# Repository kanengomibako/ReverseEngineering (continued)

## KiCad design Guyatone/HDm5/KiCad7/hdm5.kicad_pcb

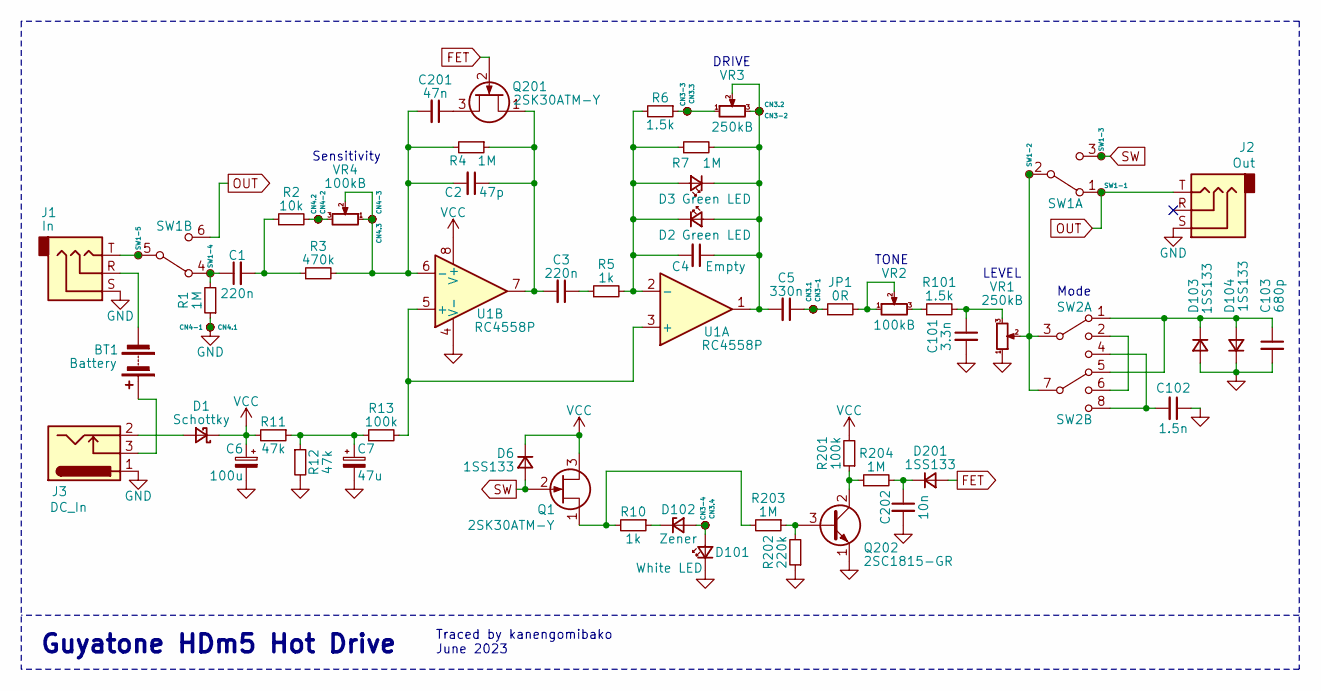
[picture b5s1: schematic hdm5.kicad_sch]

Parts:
BT1: Battery; PinHeader_1x02_P2.54mm_Vertical
C1, C3: 220n; my_C_Rect1_P5.00mm
C2: 47p; my_C_Disc_P2.50mm
C4: Empty; my_C_Disc_P2.50mm
C5: 330n; my_C_Rect1_P5.00mm
C6: 100u; my_C_D5.0mm_P2.50mm
C7: 47u; my_C_D5.0mm_P2.50mm
C101: 3.3n; my_C_Disc_P2.50mm
C102: 1.5n; my_C_Disc_P2.50mm
C103: 680p; C_Rect_L11.0mm_W2.8mm_P10.00mm_MKT
C201: 47n; my_C_Rect1_P5.00mm
C202: 10n; my_C_Rect1_P5.00mm
CN3-1, CN3-2, CN3-3, CN3-4, CN3.1, CN3.2, CN3.3, CN3.4, CN4-1, CN4-2, CN4-3, CN4.1, CN4.2, CN4.3: tp; my_SmallestPad_0-72mmDrill
D1: Schottky; D_A-405_P7.62mm_Horizontal
D2, D3: Green LED; my_LED_3mm
D6, D103, D104, D201: 1SS133; D_A-405_P5.08mm_Vertical_KathodeUp
D101: White LED; my_LED_3mm
D102: Zener; D_A-405_P5.08mm_Vertical_KathodeUp
J1: In; Audio_Jack_EX
J2: Out; Audio_Jack_EX
J3: DC_In; my_DC_Jack
JP1: 0R; R_Axial_DIN0204_L3.6mm_D1.6mm_P5.08mm_Vertical
Q1, Q201: 2SK30ATM-Y; TO-92L_Wide
Q202: 2SC1815-GR; TO-92L_Wide
R1, R203, R204: 1M; R_Axial_DIN0204_L3.6mm_D1.6mm_P5.08mm_Vertical
R2: 10k; R_Axial_DIN0204_L3.6mm_D1.6mm_P5.08mm_Vertical
R3: 470k; R_Axial_DIN0204_L3.6mm_D1.6mm_P2.54mm_Vertical
R4, R7: 1M; R_Axial_DIN0204_L3.6mm_D1.6mm_P2.54mm_Vertical
R5, R10: 1k; R_Axial_DIN0204_L3.6mm_D1.6mm_P5.08mm_Vertical
R6: 1.5k; R_Axial_DIN0204_L3.6mm_D1.6mm_P2.54mm_Vertical
R11, R12: 47k; R_Axial_DIN0204_L3.6mm_D1.6mm_P5.08mm_Vertical
R13: 100k; R_Axial_DIN0204_L3.6mm_D1.6mm_P5.08mm_Vertical
R101: 1.5k; R_Axial_DIN0204_L3.6mm_D1.6mm_P5.08mm_Vertical
R201: 100k; R_Axial_DIN0204_L3.6mm_D1.6mm_P2.54mm_Vertical
R202: 220k; R_Axial_DIN0204_L3.6mm_D1.6mm_P2.54mm_Vertical
SW1: SW1; PinHeader_2x03_P2.54mm_Vertical
SW1-1, SW1-2, SW1-3, SW1-4, SW1-5: tp; my_SmallestPad_0-72mmDrill
SW2: SW2; PinHeader_2x04_P2.54mm_Vertical
U1: RC4558P; DIP-8_W7.62mm_Socket
VR1, VR3: 250kB; PinHeader_1x03_P2.54mm_Vertical
VR2, VR4: 100kB; PinHeader_1x03_P2.54mm_Vertical

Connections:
FET: D201.2 (A), Q201.2 (G)
GND: C6.2, C7.2, C101.2, C102.1, C103.2, C202.2, CN4-1.1, CN4.1.1, D101.1 (K), D103.2 (A), D104.1 (K), J1.S, J2.S, J3.1, Q202.1 (E), R1.1, R12.2, R202.1, U1.4 (V-), VR1.1
unnamed: BT1.1 (+), J3.3
unnamed: BT1.2 (-), J1.R
unnamed: C1.1, R1.2, SW1.4 (A), SW1-4.1
unnamed: C1.2, R2.1, R3.1
unnamed: C3.1, R5.1
unnamed: C5.1, CN3-1.1, CN3.1.1, JP1.1
unnamed: C7.1, R11.1, R12.1, R13.1
unnamed: C101.1, R101.2, VR1.3
unnamed: C102.2, SW2.4, SW2.8
unnamed: CN3-3.1, CN3.3.1, R6.1, VR3.1
unnamed: CN4-2.1, CN4.2.1, R2.2, VR4.3
unnamed: D1.2 (A), J3.2
unnamed: C4.1, C5.2, CN3-2.1, CN3.2.1, D2.2 (A), D3.1 (K), R7.2, U1.1, VR3.2, VR3.3
unnamed: C4.2, D2.1 (K), D3.2 (A), R5.2, R6.2, R7.1, U1.2 (-)
unnamed: CN3-4.1, CN3.4.1, D101.2 (A), D102.2 (A)
unnamed: D102.1 (K), R10.1
unnamed: C103.1, D103.1 (K), D104.2 (A), SW2.1, SW2.5
unnamed: C202.1, D201.1 (K), R204.2
unnamed: J1.T, SW1.5 (B), SW1-5.1
unnamed: JP1.2, VR2.1, VR2.2
unnamed: Q1.1 (S), R10.2, R203.2
unnamed: C201.1, Q201.3 (D)
unnamed: C2.1, C3.2, Q201.1 (S), R4.1, U1.7
unnamed: Q202.3 (B), R202.2, R203.1
unnamed: Q202.2 (C), R201.1, R204.1
unnamed: R101.1, VR2.3
unnamed: SW1.2 (B), SW1-2.1, SW2.3, SW2.7, VR1.2
unnamed: SW2.2, SW2.6
unnamed: R13.2, U1.3 (+), U1.5 (+)
unnamed: C2.2, C201.2, CN4-3.1, CN4.3.1, R3.2, R4.2, U1.6 (-), VR4.1, VR4.2
OUT: J2.T, SW1.1 (A), SW1.6 (C), SW1-1.1
SW: D6.2 (A), Q1.2 (G), SW1.3 (C), SW1-3.1
VCC: C6.1, D1.1 (K), D6.1 (K), Q1.3 (D), R11.2, R201.2, U1.8 (V+)

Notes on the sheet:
TONE
Guyatone HDm5 Hot Drive
Mode
Sensitivity
DRIVE
Traced by kanengomibako June 2023
LEVEL

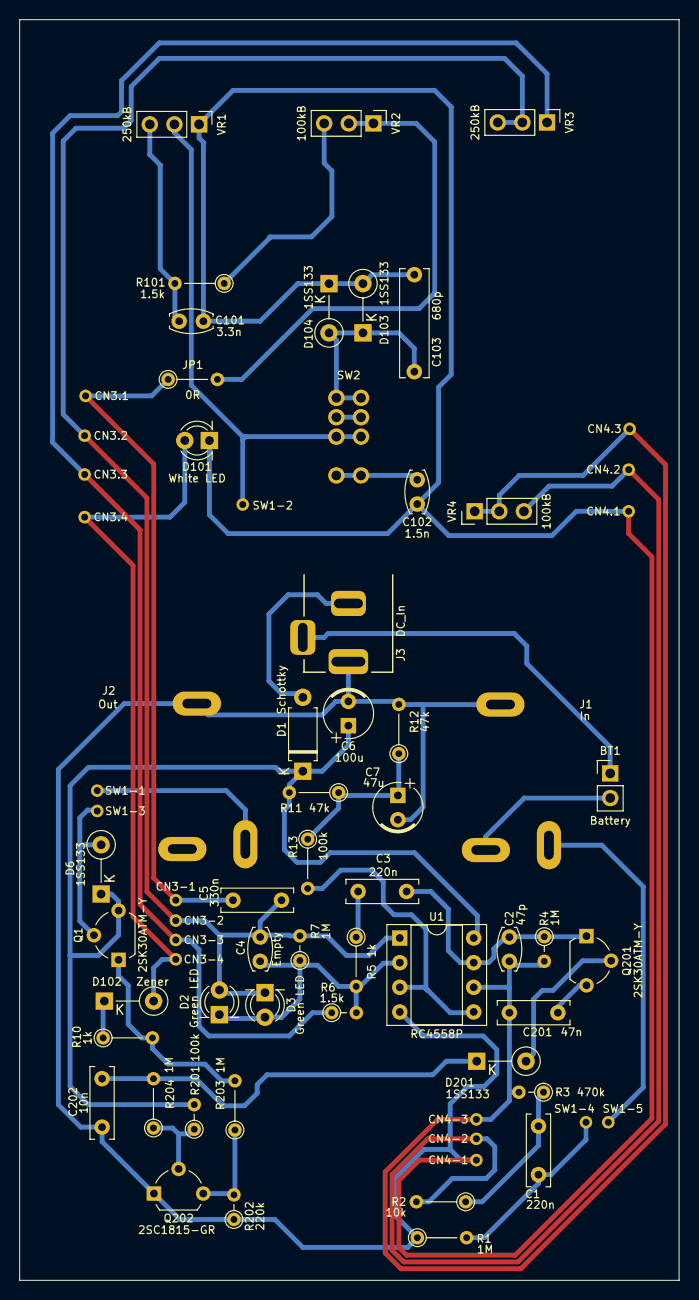
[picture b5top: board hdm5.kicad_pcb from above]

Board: 2 copper layers, 68.0 x 130.0 mm, 70 parts (0 on the bottom side), 35 nets.

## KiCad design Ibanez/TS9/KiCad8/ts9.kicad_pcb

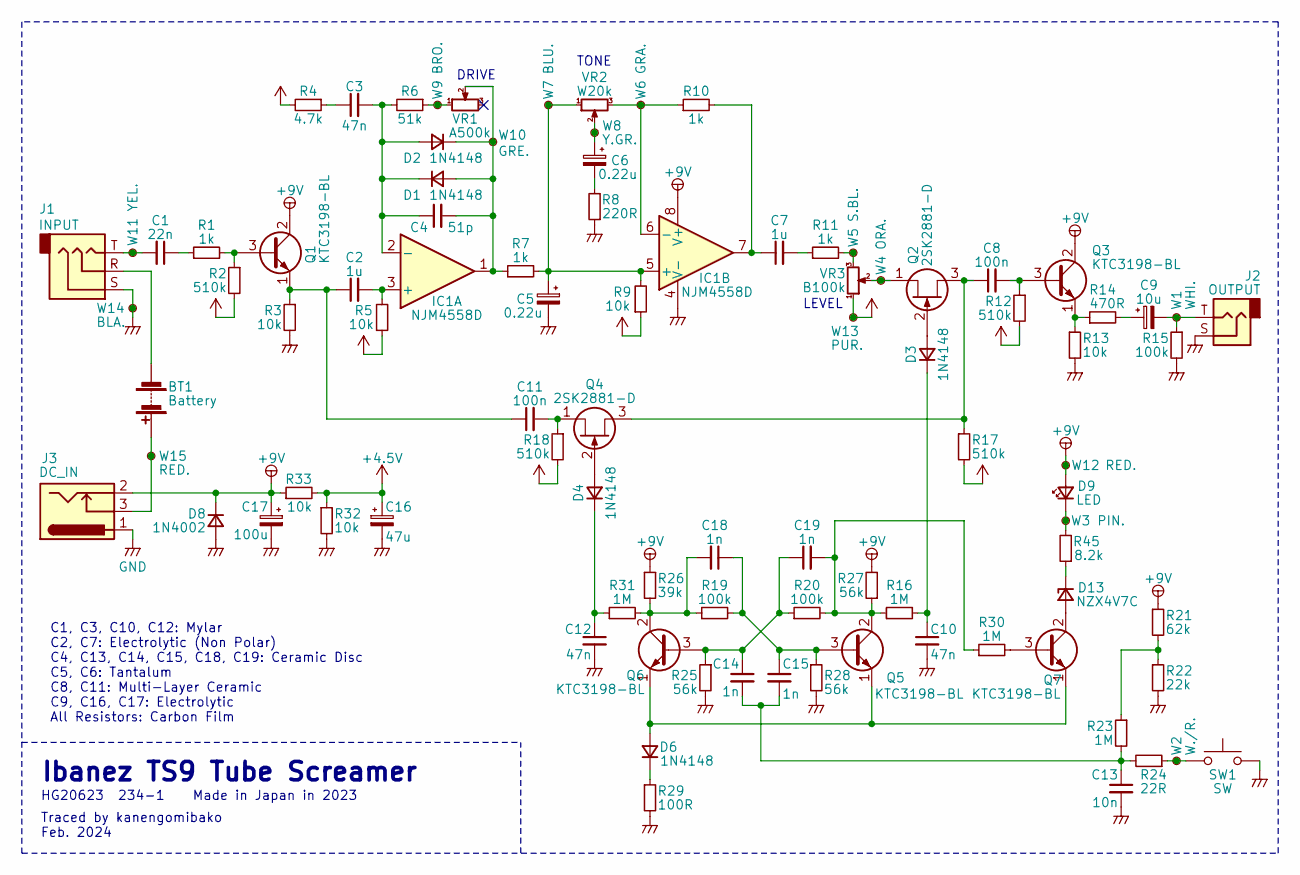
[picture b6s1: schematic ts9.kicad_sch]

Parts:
BT1: Battery; my_conn
C1: 22n; C_Disc_D4.3mm_W1.9mm_P5.00mm
C2, C7: 1u; my_C_NP_P2.50mm
C3, C10, C12: 47n; C_Disc_D4.3mm_W1.9mm_P5.00mm
C4: 51p; C_Disc_D3.0mm_W1.6mm_P2.50mm
C5: 0.22u; CP_Radial_Tantal_D4.5mm_P5.00mm
C6: 0.22u; CP_Radial_Tantal_D4.5mm_P2.50mm
C8, C11: 100n; C_Axial_L3.8mm_D2.6mm_P7.50mm_Horizontal
C9: 10u; my_C_D5.0mm_P2.50mm
C13: 10n; C_Disc_D4.3mm_W1.9mm_P5.00mm
C14, C15, C18, C19: 1n; C_Disc_D4.3mm_W1.9mm_P5.00mm
C16: 47u; my_C_D5.0mm_P2.50mm
C17: 100u; CP_Radial_D8.0mm_P5.00mm
D1, D2: 1N4148; D_DO-35_SOD27_P3.81mm_Vertical_AnodeUp
D3, D4, D6: 1N4148; D_T-1_P5.08mm_Horizontal
D8: 1N4002; D_DO-35_SOD27_P10.16mm_Horizontal
D9: LED; my_conn
D13: NZX4V7C; D_T-1_P5.08mm_Horizontal
IC1: NJM4558D; DIP-8_W7.62mm
J1: INPUT
J2: OUTPUT
J3: DC_IN; my_DC_Jack
Q1, Q3, Q5, Q6, Q7: KTC3198-BL; TO-92_Inline_Wide
Q2, Q4: 2SK2881-D; TO-92_Inline_Wide
R1, R7, R10, R11: 1k; R_Axial_DIN0204_L3.6mm_D1.6mm_P5.08mm_Horizontal
R2, R12, R17, R18: 510k; R_Axial_DIN0204_L3.6mm_D1.6mm_P5.08mm_Horizontal
R3, R13, R32, R33: 10k; R_Axial_DIN0204_L3.6mm_D1.6mm_P5.08mm_Horizontal
R4: 4.7k; my_R_P6mm_Horizontal
R5: 10k; my_R_P6mm_Horizontal
R6: 51k; R_Axial_DIN0204_L3.6mm_D1.6mm_P5.08mm_Horizontal
R8: 220R; R_Axial_DIN0204_L3.6mm_D1.6mm_P5.08mm_Horizontal
R9: 10k; R_Axial_DIN0204_L3.6mm_D1.6mm_P7.62mm_Horizontal
R14: 470R; R_Axial_DIN0204_L3.6mm_D1.6mm_P5.08mm_Horizontal
R15, R19, R20: 100k; R_Axial_DIN0204_L3.6mm_D1.6mm_P5.08mm_Horizontal
R16, R23, R30, R31: 1M; R_Axial_DIN0204_L3.6mm_D1.6mm_P5.08mm_Horizontal
R21: 62k; R_Axial_DIN0204_L3.6mm_D1.6mm_P5.08mm_Horizontal
R22: 22k; R_Axial_DIN0204_L3.6mm_D1.6mm_P5.08mm_Horizontal
R24: 22R; R_Axial_DIN0204_L3.6mm_D1.6mm_P5.08mm_Horizontal
R25, R27, R28: 56k; R_Axial_DIN0204_L3.6mm_D1.6mm_P5.08mm_Horizontal
R26: 39k; R_Axial_DIN0204_L3.6mm_D1.6mm_P5.08mm_Horizontal
R29: 100R; R_Axial_DIN0204_L3.6mm_D1.6mm_P5.08mm_Horizontal
R45: 8.2k; R_Axial_DIN0204_L3.6mm_D1.6mm_P5.08mm_Horizontal
SW1: SW
VR1: A500k
VR2: W20k
VR3: B100k
W1: WHI.; my_WirePad_0-8mmDrill
W2: W./R.; my_WirePad_0-8mmDrill
W3: PIN.; my_WirePad_0-8mmDrill
W4: ORA.; my_WirePad_0-8mmDrill
W5: S.BL.; my_WirePad_0-8mmDrill
W6: GRA.; my_WirePad_0-8mmDrill
W7: BLU.; my_WirePad_0-8mmDrill
W8: Y.GR.; my_WirePad_0-8mmDrill
W9: BRO.; my_WirePad_0-8mmDrill
W10: GRE.; my_WirePad_0-8mmDrill
W11: YEL.; my_WirePad_0-8mmDrill
W12, W15: RED.; my_WirePad_0-8mmDrill
W13: PUR.; my_WirePad_0-8mmDrill
W14: BLA.; my_WirePad_0-8mmDrill

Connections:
+4.5V: C16.1, R2.2, R4.2, R5.1, R9.1, R12.2, R17.2, R18.2, R32.1, R33.2, VR3.1, W13.1
+9V: C17.1, D8.1 (K), D9.2 (A), IC1.8 (V+), J3.2, Q1.2 (C), Q3.2 (C), R21.1, R26.1, R27.2, R33.1, W12.1
GND: C5.2, C10.2, C12.2, C13.2, C16.2, C17.2, D8.2 (A), IC1.4 (V-), J1.S, J2.S, J3.1, R3.2, R8.1, R13.2, R15.2, R22.2, R25.2, R28.2, R29.2, R32.2, SW1.2, W14.1
unnamed: BT1.2 (-), J1.R
unnamed: C1.1, R1.1
unnamed: C1.2, J1.T, W11.1
unnamed: C3.1, R4.1
unnamed: C6.1, VR2.2, W8.1
unnamed: C6.2, R8.2
unnamed: C7.1, IC1.7, R10.2
unnamed: C7.2, R11.1
unnamed: C9.1, R14.2
unnamed: C9.2, J2.T, R15.1, W1.1
unnamed: C13.1, C14.2, C15.2, R23.2, R24.2
unnamed: C4.2, D1.2 (A), D2.1 (K), IC1.1, R7.1, VR1.2, W10.1
unnamed: C3.2, C4.1, D1.1 (K), D2.2 (A), IC1.2 (-), R6.2
unnamed: D3.2 (A), Q2.2 (G)
unnamed: C10.1, D3.1 (K), R16.2
unnamed: D4.2 (A), Q4.2 (G)
unnamed: C12.1, D4.1 (K), R31.1
unnamed: D6.2 (A), Q5.1 (E), Q6.1 (E), Q7.1 (E)
unnamed: D6.1 (K), R29.1
unnamed: D13.2 (A), Q7.2 (C)
unnamed: D13.1 (K), R45.1
unnamed: C2.2, IC1.3 (+), R5.2
unnamed: C5.1, IC1.5 (+), R7.2, R9.2, VR2.1, W7.1
unnamed: IC1.6 (-), R10.1, VR2.3, W6.1
unnamed: BT1.1 (+), J3.3, W15.1
unnamed: Q1.3 (B), R1.2, R2.1
unnamed: C2.1, C11.1, Q1.1 (E), R3.1
unnamed: C8.1, Q2.3 (D), Q4.3 (D), R17.1
unnamed: Q2.1 (S), VR3.2, W4.1
unnamed: C8.2, Q3.3 (B), R12.1
unnamed: Q3.1 (E), R13.1, R14.1
unnamed: C11.2, Q4.1 (S), R18.1
unnamed: C15.1, C18.1, Q5.3 (B), R19.2, R28.1
unnamed: C19.2, Q5.2 (C), R16.1, R20.2, R27.1, R30.1
unnamed: C14.1, C19.1, Q6.3 (B), R20.1, R25.1
unnamed: C18.2, Q6.2 (C), R19.1, R26.2, R31.2
unnamed: Q7.3 (B), R30.2
unnamed: R6.1, VR1.1, W9.1
unnamed: R11.2, VR3.3, W5.1
unnamed: R21.2, R22.1, R23.1
unnamed: R24.1, SW1.1, W2.1
unnamed: D9.1 (K), R45.2, W3.1

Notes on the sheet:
Ibanez TS9 Tube Screamer
HG20623 234-1 Made in Japan in 2023
DRIVE
Traced by kanengomibako Feb. 2024
LEVEL
TONE
C1, C3, C10, C12: Mylar C2, C7: Electrolytic (Non Polar) C4, C13, C14, C15, C18, C19: Ceramic Disc C5, C6: Tantalum C8, C11: Multi-Layer Ceramic C9, C16, C17: Electrolytic All Resistors: Carbon Film

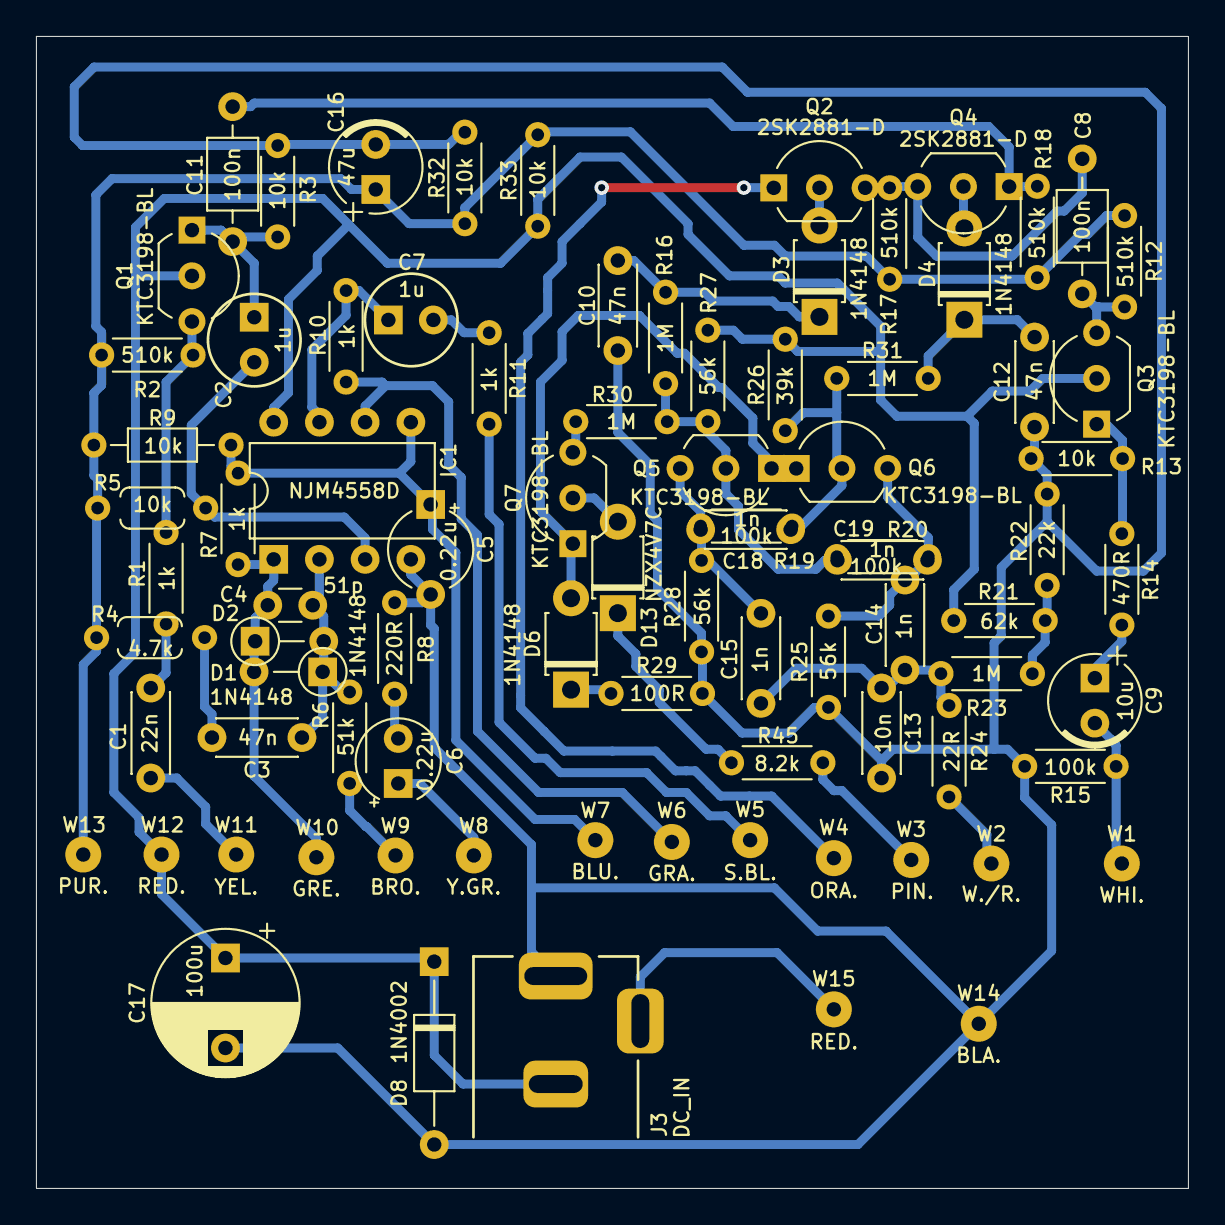
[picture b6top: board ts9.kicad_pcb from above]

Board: 2 copper layers, 64.0 x 64.0 mm, 84 parts (0 on the bottom side), 44 nets.

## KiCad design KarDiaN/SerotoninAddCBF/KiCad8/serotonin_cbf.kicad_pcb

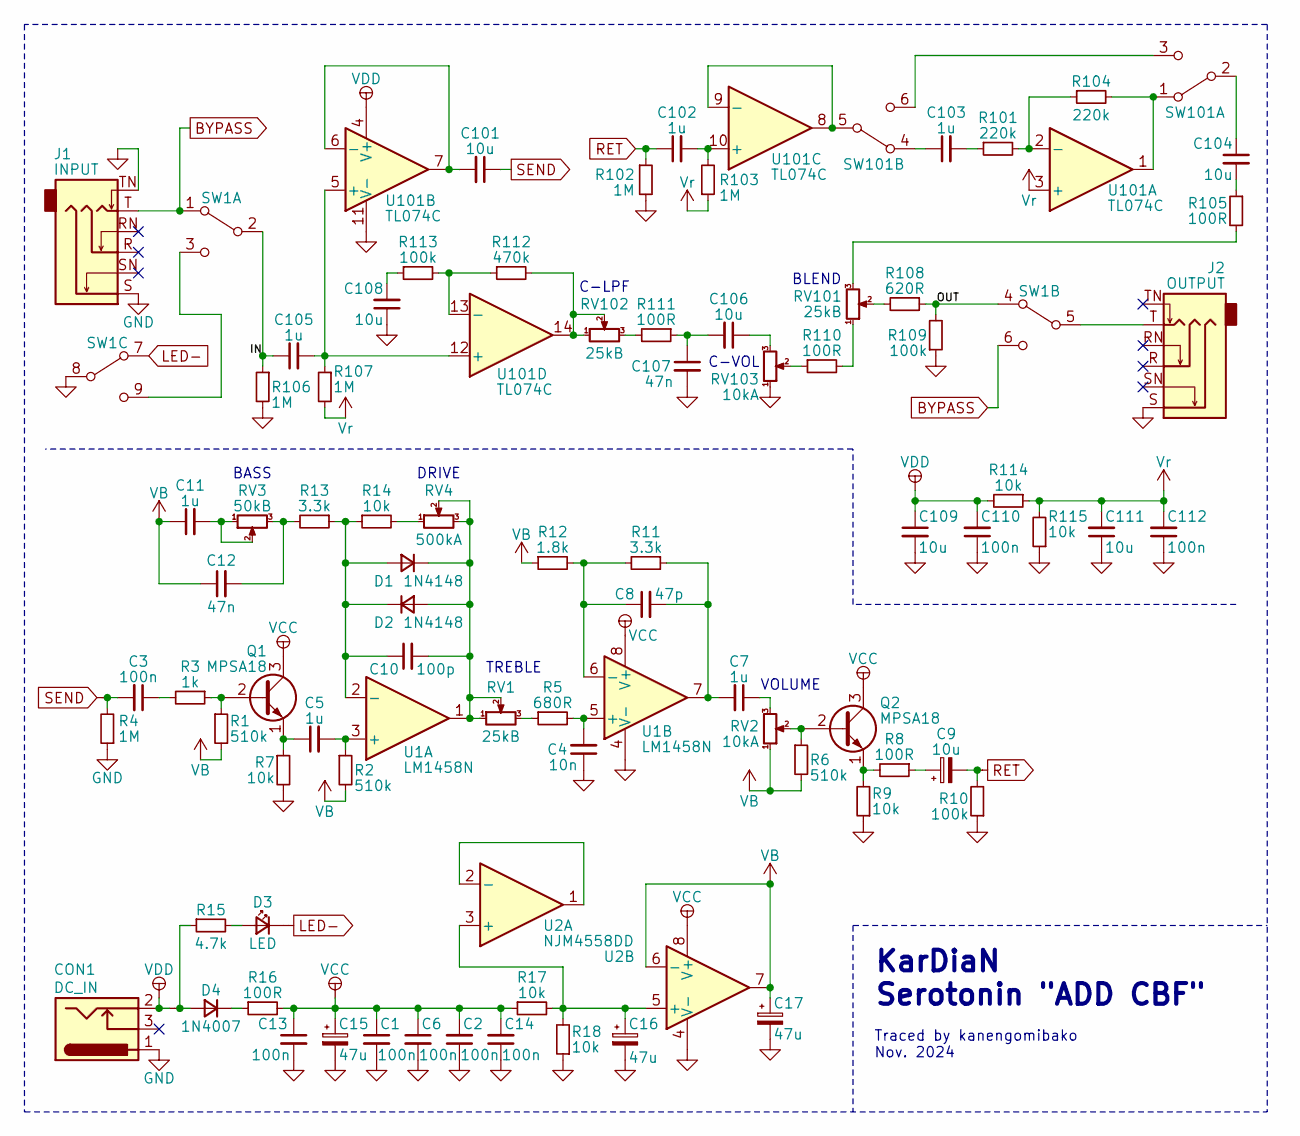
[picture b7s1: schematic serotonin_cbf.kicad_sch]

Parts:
C1, C2, C6, C13, C14: 100n; C_Rect_L7.0mm_W2.0mm_P5.00mm
C3: 100n; R_Axial_DIN0414_L11.9mm_D4.5mm_P15.24mm_Horizontal
C4: 10n; C_Rect_L7.0mm_W2.0mm_P5.00mm
C5, C11: 1u; C_Rect_L7.0mm_W2.0mm_P5.00mm
C7: 1u; R_Axial_DIN0414_L11.9mm_D4.5mm_P15.24mm_Horizontal
C8: 47p; C_Rect_L7.0mm_W2.0mm_P5.00mm
C9: 10u; CP_Radial_D8.0mm_P2.50mm
C10: 100p; C_Rect_L7.0mm_W2.0mm_P5.00mm
C12: 47n; C_Rect_L7.0mm_W2.0mm_P5.00mm
C15, C16, C17: 47u; CP_Radial_D8.0mm_P2.50mm
C101, C104, C106, C108, C109, C111: 10u; C_1206_3216Metric
C102, C103, C105: 1u; C_0805_2012Metric
C107: 47n; C_0805_2012Metric
C110, C112: 100n; C_0805_2012Metric
CN1: 006; my_conn
CN2: LED; my_conn
CN3: IN; my_conn
CN4: OUT; my_conn
CON1: DC_IN; my_DC_Jack
D1, D2: 1N4148; my_D_P5.08mm_Horizontal
D3: LED; my_LED_5mm
D4: 1N4007; D_DO-35_SOD27_P7.62mm_Horizontal
J1: INPUT; my_Phone_Jack_Daier
J2: OUTPUT; my_Phone_Jack_Daier
Q1, Q2: MPSA18; TO-92_Inline_Wide
R1, R2, R6: 510k; R_Axial_DIN0207_L6.3mm_D2.5mm_P10.16mm_Horizontal
R3: 1k; R_Axial_DIN0414_L11.9mm_D4.5mm_P15.24mm_Horizontal
R4: 1M; R_Axial_DIN0207_L6.3mm_D2.5mm_P10.16mm_Horizontal
R5: 680R; R_Axial_DIN0414_L11.9mm_D4.5mm_P15.24mm_Horizontal
R7, R9, R14, R17, R18: 10k; R_Axial_DIN0207_L6.3mm_D2.5mm_P10.16mm_Horizontal
R8, R16: 100R; R_Axial_DIN0207_L6.3mm_D2.5mm_P10.16mm_Horizontal
R10: 100k; R_Axial_DIN0207_L6.3mm_D2.5mm_P10.16mm_Horizontal
R11, R13: 3.3k; R_Axial_DIN0207_L6.3mm_D2.5mm_P10.16mm_Horizontal
R12: 1.8k; R_Axial_DIN0207_L6.3mm_D2.5mm_P10.16mm_Horizontal
R15: 4.7k; R_Axial_DIN0207_L6.3mm_D2.5mm_P10.16mm_Horizontal
R101, R104: 220k; R_0805_2012Metric
R102, R103, R106, R107: 1M; R_0805_2012Metric
R105, R110, R111: 100R; R_0805_2012Metric
R108: 620R; R_0805_2012Metric
R109, R113: 100k; R_0805_2012Metric
R112: 470k; R_0805_2012Metric
R114, R115: 10k; R_0805_2012Metric
RV1: 25kB; my_pot_5mm
RV2: 10kA; my_pot_5mm
RV3: 50kB; my_pot_5mm
RV4: 500kA; my_pot_5mm
RV101, RV102: 25kB; PinHeader_1x03_P2.54mm_Vertical
RV103: 10kA; PinHeader_1x03_P2.54mm_Vertical
SW1: SW1; my_sw_3pdt
SW101: SW101; PinHeader_2x03_P2.54mm_Vertical
U1: LM1458N; DIP-8_W7.62mm
U2: NJM4558DD; DIP-8_W7.62mm
U101: TL074C; SO-14_5.3x10.2mm_P1.27mm

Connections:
/IN: C105.1, R106.1, SW1.2 (B)
/OUT: R108.1, R109.2, SW1.4 (A)
BYPASS: J1.T, SW1.1 (A), SW1.6 (C)
GND: C1.2, C2.1, C4.1, C6.2, C13.2, C14.1, C15.2, C16.2, C17.2, C107.2, C108.1, C109.2, C110.1, C111.1, C112.1, CON1.1, J1.S, J1.TN, J2.S, R4.1, R7.2, R9.1, R10.1, R18.1, R102.2, R106.2, R109.1, R115.1, RV103.1, SW1.8 (B), U1.4 (V-), U2.4 (V-), U101.11 (V-); also elsewhere on the board
LED-: CN2.1, SW1.7 (A)
unnamed: C3.1, R3.2
unnamed: C3.2, CN3.2, R4.2
unnamed: C7.1, RV2.3
unnamed: C7.2, C8.2, R11.1, U1.7
unnamed: C9.1, R8.1
unnamed: C9.2, CN4.2, R10.2
unnamed: C11.2, RV3.1, RV3.2
unnamed: C12.2, R13.2, RV3.3
unnamed: C103.2, R101.1
unnamed: C104.2, R105.1
unnamed: C106.1, RV103.3
unnamed: C106.2, C107.1, R111.1
unnamed: C108.2, R113.1
unnamed: C10.1, D1.2 (A), D2.1 (K), R13.1, R14.1, U1.2 (-)
unnamed: C10.2, D1.1 (K), D2.2 (A), RV1.1, RV1.2, RV4.2, RV4.3, U1.1
unnamed: D3.2 (A), R15.2
unnamed: CN2.2, D3.1 (K)
unnamed: CN1.2, D4.2 (A), R15.1
unnamed: D4.1 (K), R16.1
unnamed: Q1.2 (B), R1.1, R3.1
unnamed: C5.1, Q1.1 (E), R7.1
unnamed: Q2.2 (B), R6.1, RV2.2
unnamed: Q2.1 (E), R8.2, R9.2
unnamed: R5.1, RV1.3
unnamed: R14.2, RV4.1
unnamed: R105.2, RV101.3
unnamed: R108.2, RV101.2
unnamed: R110.1, RV103.2
unnamed: R110.2, RV101.1
unnamed: R111.2, RV102.3
unnamed: R112.2, RV102.1, RV102.2, U101.14
unnamed: SW1.3 (C), SW1.9 (C)
unnamed: J2.T, SW1.5 (B)
unnamed: R104.2, SW101.1 (A), U101.1
unnamed: C104.1, SW101.2 (B)
unnamed: SW101.3 (C), SW101.6 (C)
unnamed: C103.1, SW101.4 (A)
unnamed: SW101.5 (B), U101.8, U101.9 (-)
unnamed: C5.2, R2.1, U1.3 (+)
unnamed: C4.2, R5.2, U1.5 (+)
unnamed: C8.1, R11.2, R12.2, U1.6 (-)
unnamed: C16.1, R17.2, R18.2, U2.3 (+), U2.5 (+)
unnamed: U2.1, U2.2 (-)
unnamed: R101.2, R104.1, U101.2 (-)
unnamed: C105.2, R107.1, U101.5 (+), U101.12 (+)
unnamed: C101.2, U101.6 (-), U101.7
unnamed: C102.2, R103.2, U101.10 (+)
unnamed: R112.1, R113.2, U101.13 (-)
RET: C102.1, CN4.1, R102.1
SEND: C101.1, CN3.1
VB: C11.1, C12.1, C17.1, R1.2, R2.2, R6.2, R12.1, RV2.1, U2.6 (-), U2.7
VCC: C1.1, C2.2, C6.1, C13.1, C14.2, C15.1, Q1.3 (C), Q2.3 (C), R16.2, R17.1, U1.8 (V+), U2.8 (V+)
VDD: C109.1, C110.2, CN1.1, CON1.2, R114.2, U101.4 (V+)
Vr: C111.2, C112.2, R103.1, R107.2, R114.1, R115.2, U101.3 (+)

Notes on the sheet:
VOLUME
KarDiaN Serotonin "ADD CBF"
C-LPF
C-VOL
Traced by kanengomibako Nov. 2024
BASS
TREBLE
DRIVE
BLEND

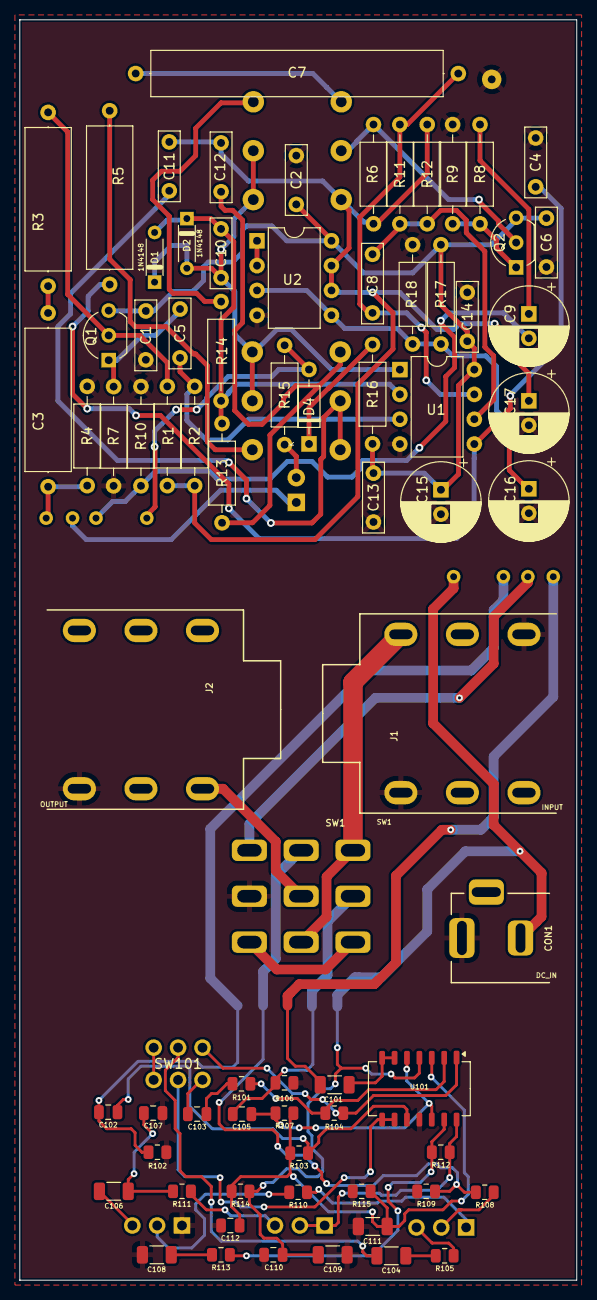
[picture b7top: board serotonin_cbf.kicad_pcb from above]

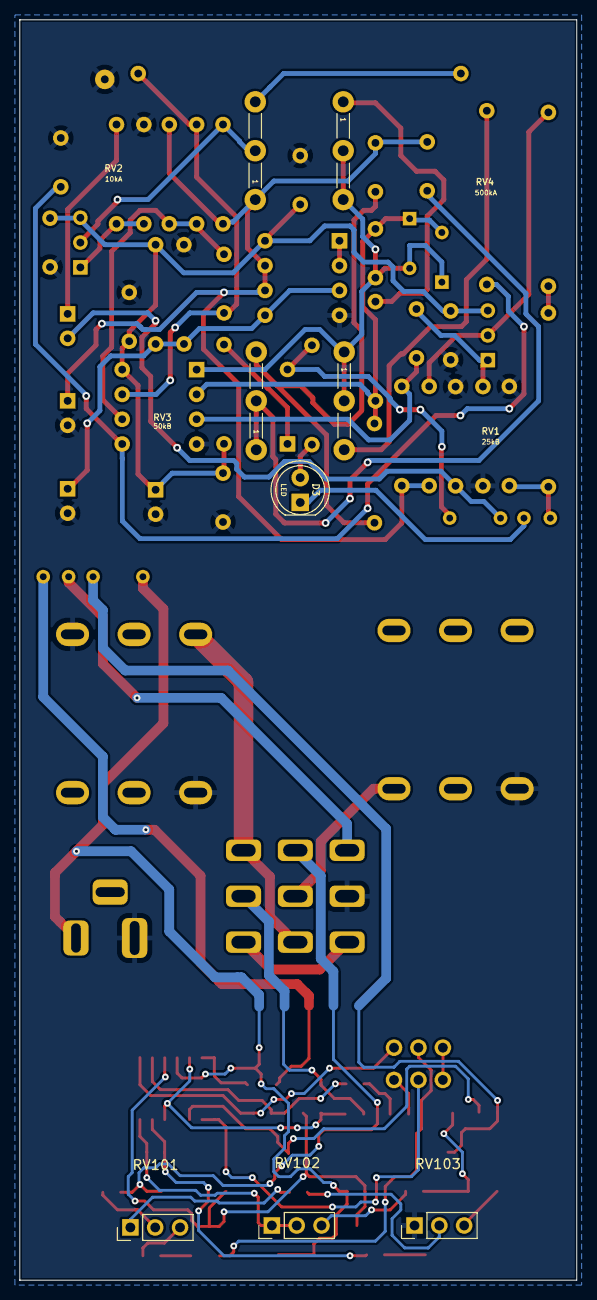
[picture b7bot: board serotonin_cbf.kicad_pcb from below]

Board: 2 copper layers, 57.0 x 129.0 mm, 88 parts (8 on the bottom side), 59 nets.

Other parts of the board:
J99: GND; my_WirePad_0-8mmDrill

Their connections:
GND: J99.1; also elsewhere on the board

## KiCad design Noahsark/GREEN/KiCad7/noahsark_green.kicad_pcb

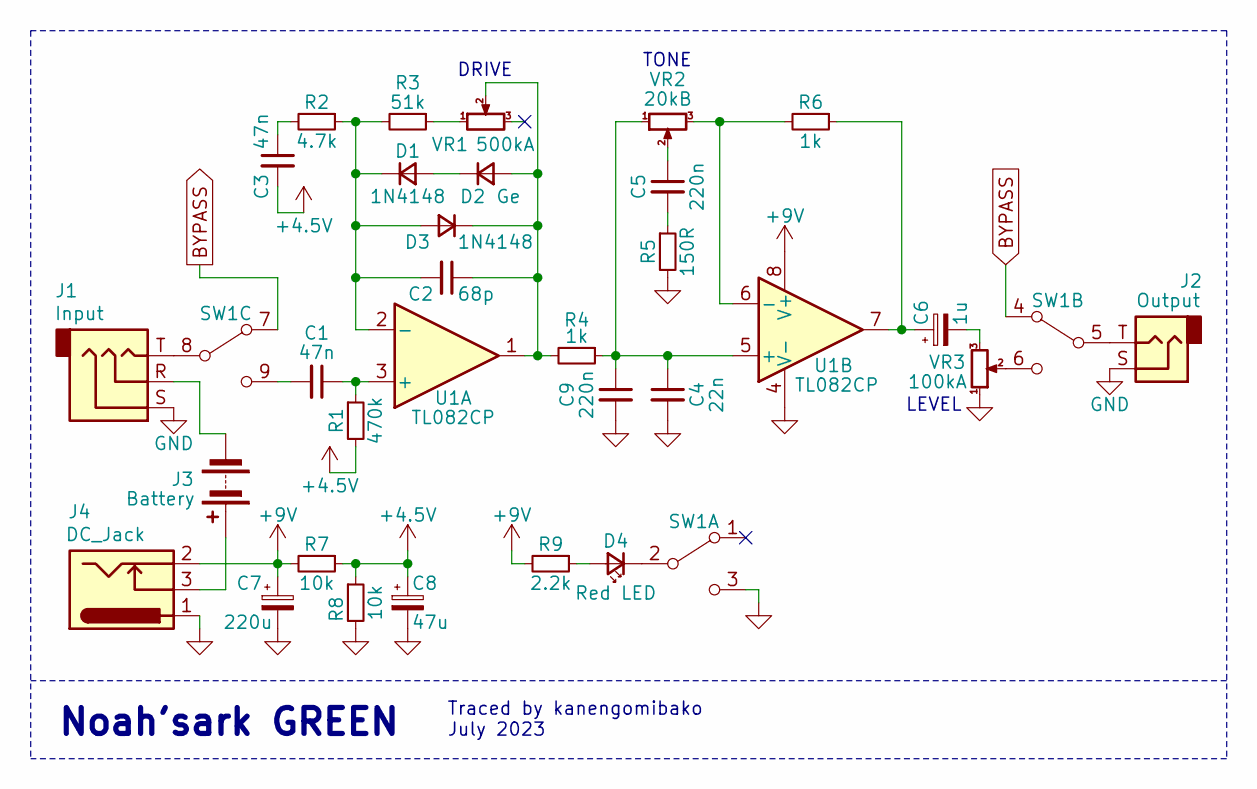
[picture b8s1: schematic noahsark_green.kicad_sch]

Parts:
C1, C3: 47n; C_Rect_L7.0mm_W2.5mm_P5.00mm
C2: 68p; C_Rect_L7.0mm_W2.5mm_P5.00mm
C4: 22n; C_Rect_L7.0mm_W2.5mm_P5.00mm
C5, C9: 220n; C_Rect_L7.0mm_W2.5mm_P5.00mm
C6: 1u; CP_Radial_D5.0mm_P2.50mm
C7: 220u; CP_Radial_D5.0mm_P2.50mm
C8: 47u; CP_Radial_D5.0mm_P2.50mm
D1, D3: 1N4148; D_DO-41_SOD81_P10.16mm_Horizontal
D2: Ge; D_DO-41_SOD81_P10.16mm_Horizontal
D4: Red LED; LED_D3.0mm
J1: Input; PinHeader_1x03_P2.54mm_Vertical
J2: Output; PinHeader_1x02_P2.54mm_Vertical
J3: Battery; PinHeader_1x02_P2.54mm_Vertical
J4: DC_Jack; PinHeader_1x03_P2.54mm_Vertical
R1: 470k; my_R_P6mm_Horizontal
R2: 4.7k; my_R_P9mm_Horizontal
R3: 51k; my_R_P9mm_Horizontal
R4, R6: 1k; my_R_P6mm_Horizontal
R5: 150R; my_R_P6mm_Horizontal
R7, R8: 10k; my_R_P9mm_Horizontal
R9: 2.2k; my_R_P6mm_Horizontal
SW1: SW; my_sw_3pdt
U1: TL082CP; DIP-8_W7.62mm
VR1: 500kA; my_pot_5mm
VR2: 20kB; my_pot_5mm
VR3: 100kA; my_pot_5mm

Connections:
+4.5V: C3.2, C8.1, R1.2, R7.1, R8.1
+9V: C7.1, J4.2, R7.2, R9.2, U1.8 (V+)
BYPASS: SW1.4 (A), SW1.7 (A)
GND: C4.2, C7.2, C8.2, C9.2, J1.S, J2.S, J4.1, R5.2, R8.2, SW1.3 (C), U1.4 (V-), VR3.1
unnamed: C3.1, R2.2
unnamed: C5.1, VR2.2
unnamed: C5.2, R5.1
unnamed: C6.1, R6.1, U1.7
unnamed: C6.2, VR3.3
unnamed: D1.2 (A), D2.1 (K)
unnamed: C2.2, D1.1 (K), D3.2 (A), R2.1, R3.2, U1.2 (-)
unnamed: C2.1, D2.2 (A), D3.1 (K), R4.2, U1.1, VR1.2
unnamed: D4.2 (A), R9.1
unnamed: D4.1 (K), SW1.2 (B)
unnamed: J3.1 (+), J4.3
unnamed: J1.R, J3.2 (-)
unnamed: R3.1, VR1.1
unnamed: J2.T, SW1.5 (B)
unnamed: SW1.6 (C), VR3.2
unnamed: J1.T, SW1.8 (B)
unnamed: C1.2, SW1.9 (C)
unnamed: C1.1, R1.1, U1.3 (+)
unnamed: C4.1, C9.1, R4.1, U1.5 (+), VR2.1
unnamed: R6.2, U1.6 (-), VR2.3

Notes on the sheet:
Noah'sark GREEN
DRIVE
Traced by kanengomibako July 2023
LEVEL
TONE

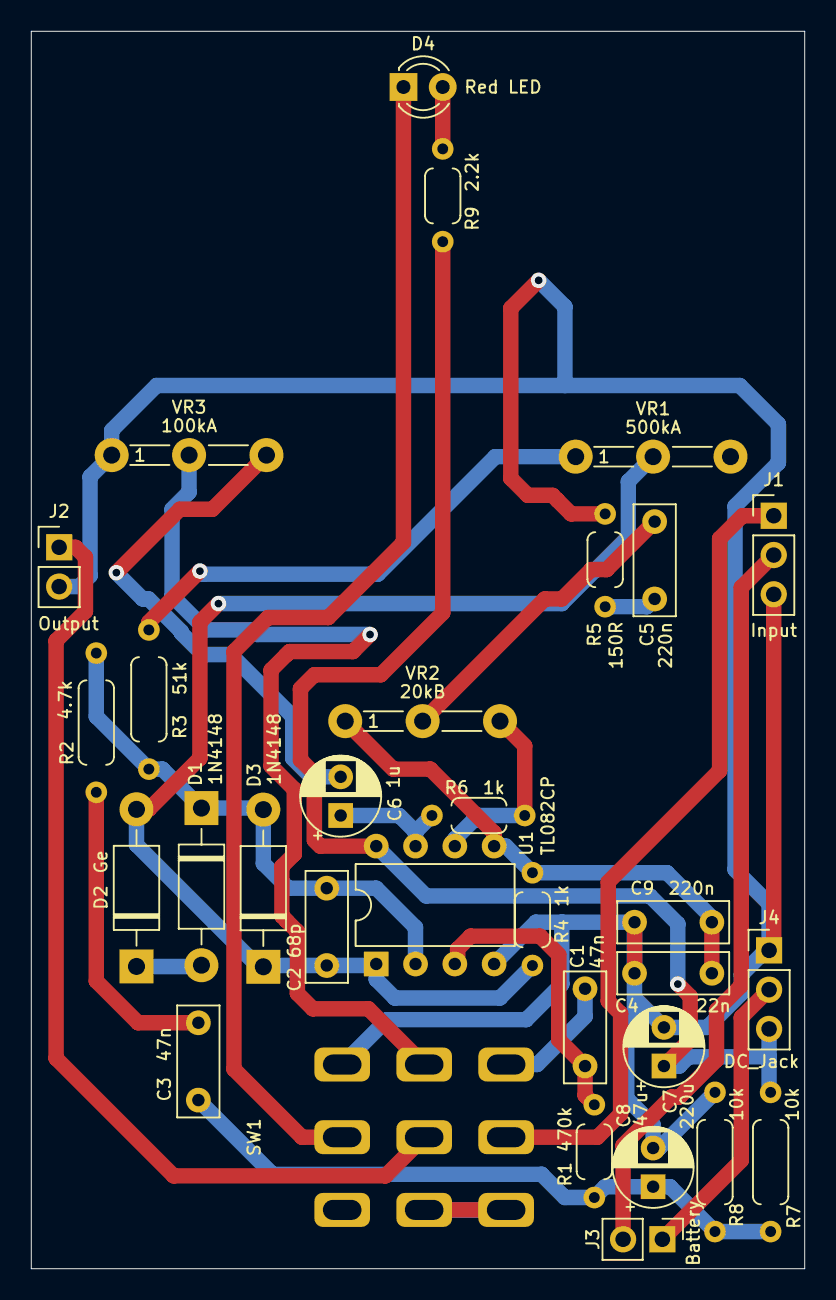
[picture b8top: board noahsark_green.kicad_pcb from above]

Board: 2 copper layers, 50.0 x 80.0 mm, 31 parts (0 on the bottom side), 24 nets.
